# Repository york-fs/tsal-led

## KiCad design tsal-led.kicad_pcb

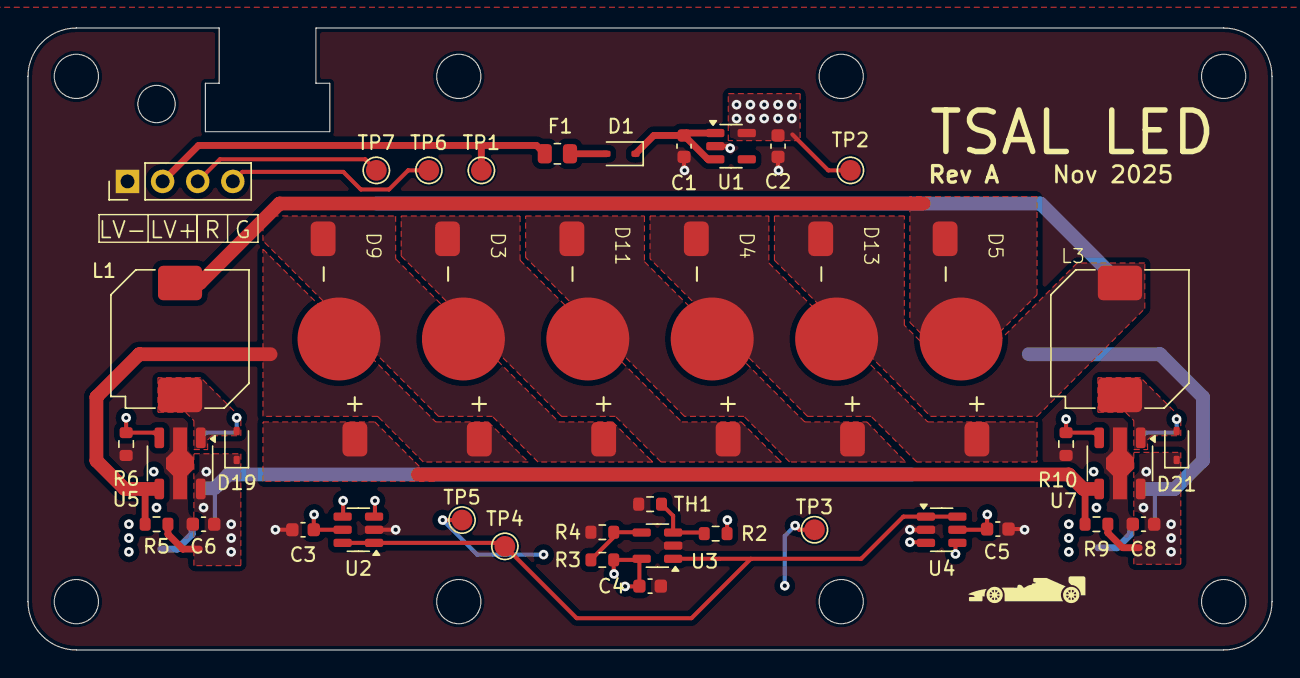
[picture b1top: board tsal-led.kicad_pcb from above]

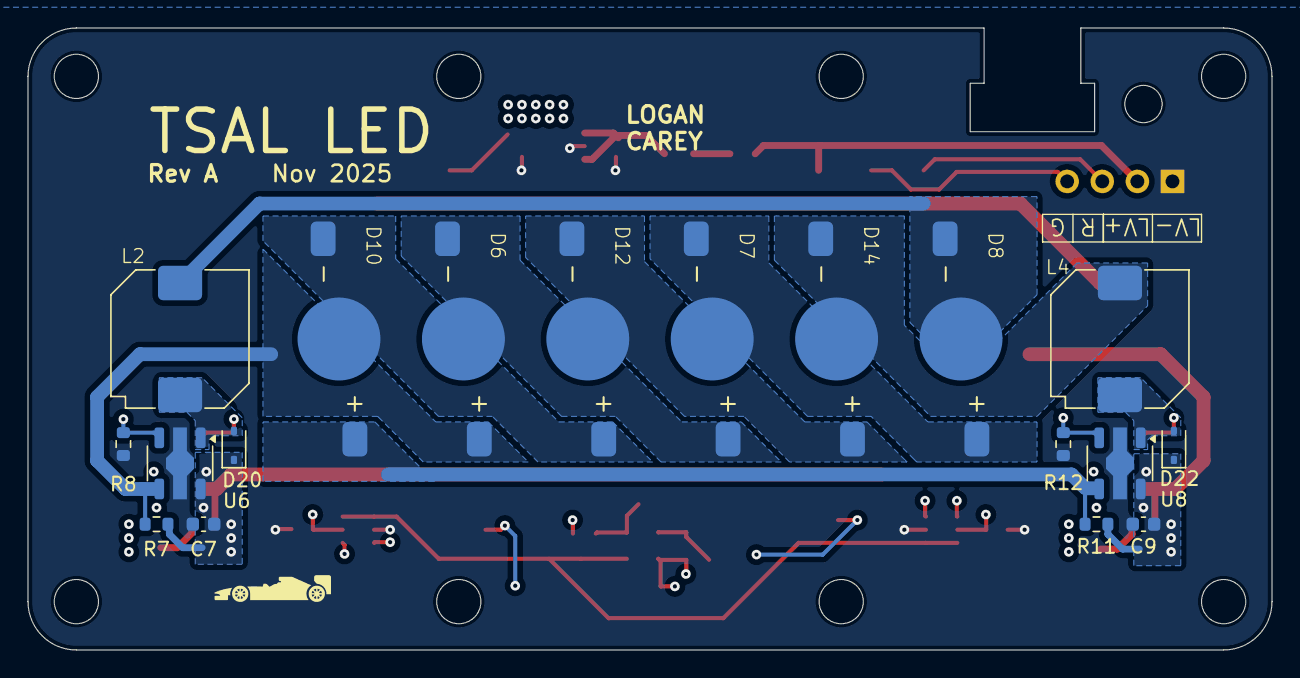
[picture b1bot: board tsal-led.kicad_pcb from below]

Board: 4 copper layers, 90.0 x 45.0 mm, 68 parts (18 on the bottom side), 32 nets.

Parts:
C1, C2, C3, C4, C5, C6, C7, C8, C9: 1u; C_0603_1608Metric
D1, D19, D20, D21, D22: NSR0530HT1G; D_SOD-323
D3, D4, D5, D6, D7, D8, D9, D10, D11, D12, D13, D14: LED; LED_SMD_8x7.3mm
F1: 100mA; R_0805_2012Metric
H1, H2, H3, H4, H5, H6, H7, H8: MountingHole_Pad; MountingHole_3.2mm_M3
H9: MountingHole; MountingHole_2.7mm_M2.5_ISO7380
J1: Molex Microfit+; PinHeader_1x04_P2.54mm_Vertical
L1, L2, L3, L4: 68u; CDRR105NP-680MC
R2, R6, R8, R10, R12: 10k; R_0603_1608Metric
R3: 30k; R_0603_1608Metric
R4: 3.3k; R_0603_1608Metric
R5, R7, R9, R11: 0.3R; R_0603_1608Metric
TH1: 10k; R_0603_1608Metric
TP1, TP2, TP3, TP4, TP5, TP6, TP7: TestPoint; TestPoint_Pad_D1.5mm
U1: AP7383; TSOT-23-5
U2, U4: 74LVC1G11; SOT-23-6
U3: LMV7219M5; SOT-23-5
U5, U6, U7, U8: PT4115; SOT-89-5

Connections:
+3.3V: C2.2, C3.2, C4.2, C5.2, R2.1, R3.1, TP2.1, U1.5 (VOUT), U2.5 (VCC), U3.5 (V+), U4.5 (VCC)
+LV: C6.2, C7.2, C8.2, C9.2, D19.1 (K), D20.1 (K), D21.1 (K), D22.1 (K), F1.1, J1.2, R5.1, R7.1, R9.1, R11.1, TP1.1, U5.5 (VIN), U6.5 (VIN), U7.5 (VIN), U8.5 (VIN)
/LED Driver1/LED_A: D6.2 (A), R7.2, U6.4 (CSN)
/LED Driver1/LED_K: D8.1 (K), L2.2
/LED Driver2/DIM: R10.1, R12.1, TP5.1, U4.4, U7.3 (DIM), U8.3 (DIM)
/LED Driver2/LED_A: D9.2 (A), R9.2, U7.4 (CSN)
/LED Driver2/LED_K: D13.1 (K), L3.2
/LED Driver3/LED_A: D10.2 (A), R11.2, U8.4 (CSN)
/LED Driver3/LED_K: D14.1 (K), L4.2
/LED Driver/DIM: R6.1, R8.1, TP3.1, U2.4, U5.3 (DIM), U6.3 (DIM)
/LED Driver/LED_A: D3.2 (A), R5.2, U5.4 (CSN)
/LED Driver/LED_K: D5.1 (K), L1.2
GND: C1.1, C2.1, C3.1, C4.1, C5.1, C6.1, C7.1, C8.1, C9.1, J1.1, R4.2, R6.2, R8.2, R10.2, R12.2, TH1.2, U1.2 (GND), U2.2 (GND), U3.2 (V-), U4.2 (GND), U5.2 (GND), U6.2 (GND), U7.2 (GND), U8.2 (GND)
GREEN: J1.4, TP6.1, U2.3
unnamed: D1.2 (A), F1.2
unnamed: C1.2, D1.1 (K), U1.1 (VIN), U1.3 (EN)
unnamed: D3.1 (K), D4.2 (A)
unnamed: D4.1 (K), D5.2 (A)
unnamed: D6.1 (K), D7.2 (A)
unnamed: D7.1 (K), D8.2 (A)
unnamed: D10.1 (K), D12.2 (A)
unnamed: D9.1 (K), D11.2 (A)
unnamed: D11.1 (K), D13.2 (A)
unnamed: D12.1 (K), D14.2 (A)
unnamed: D19.2 (A), L1.1, U5.1 (SW)
unnamed: D20.2 (A), L2.1, U6.1 (SW)
unnamed: D21.2 (A), L3.1, U7.1 (SW)
unnamed: D22.2 (A), L4.1, U8.1 (SW)
unnamed: R2.2, TH1.1, U3.3 (+)
unnamed: R3.2, R4.1, U3.4 (-)
OVERTEMP: TP4.1, U2.1, U2.6, U3.1, U4.1, U4.6
RED: J1.3, TP7.1, U4.3

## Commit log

2025-11-16 Revision A
2025-11-22 meta: Update gitignore
2025-11-22 meta: Set LF line endings explicitly
